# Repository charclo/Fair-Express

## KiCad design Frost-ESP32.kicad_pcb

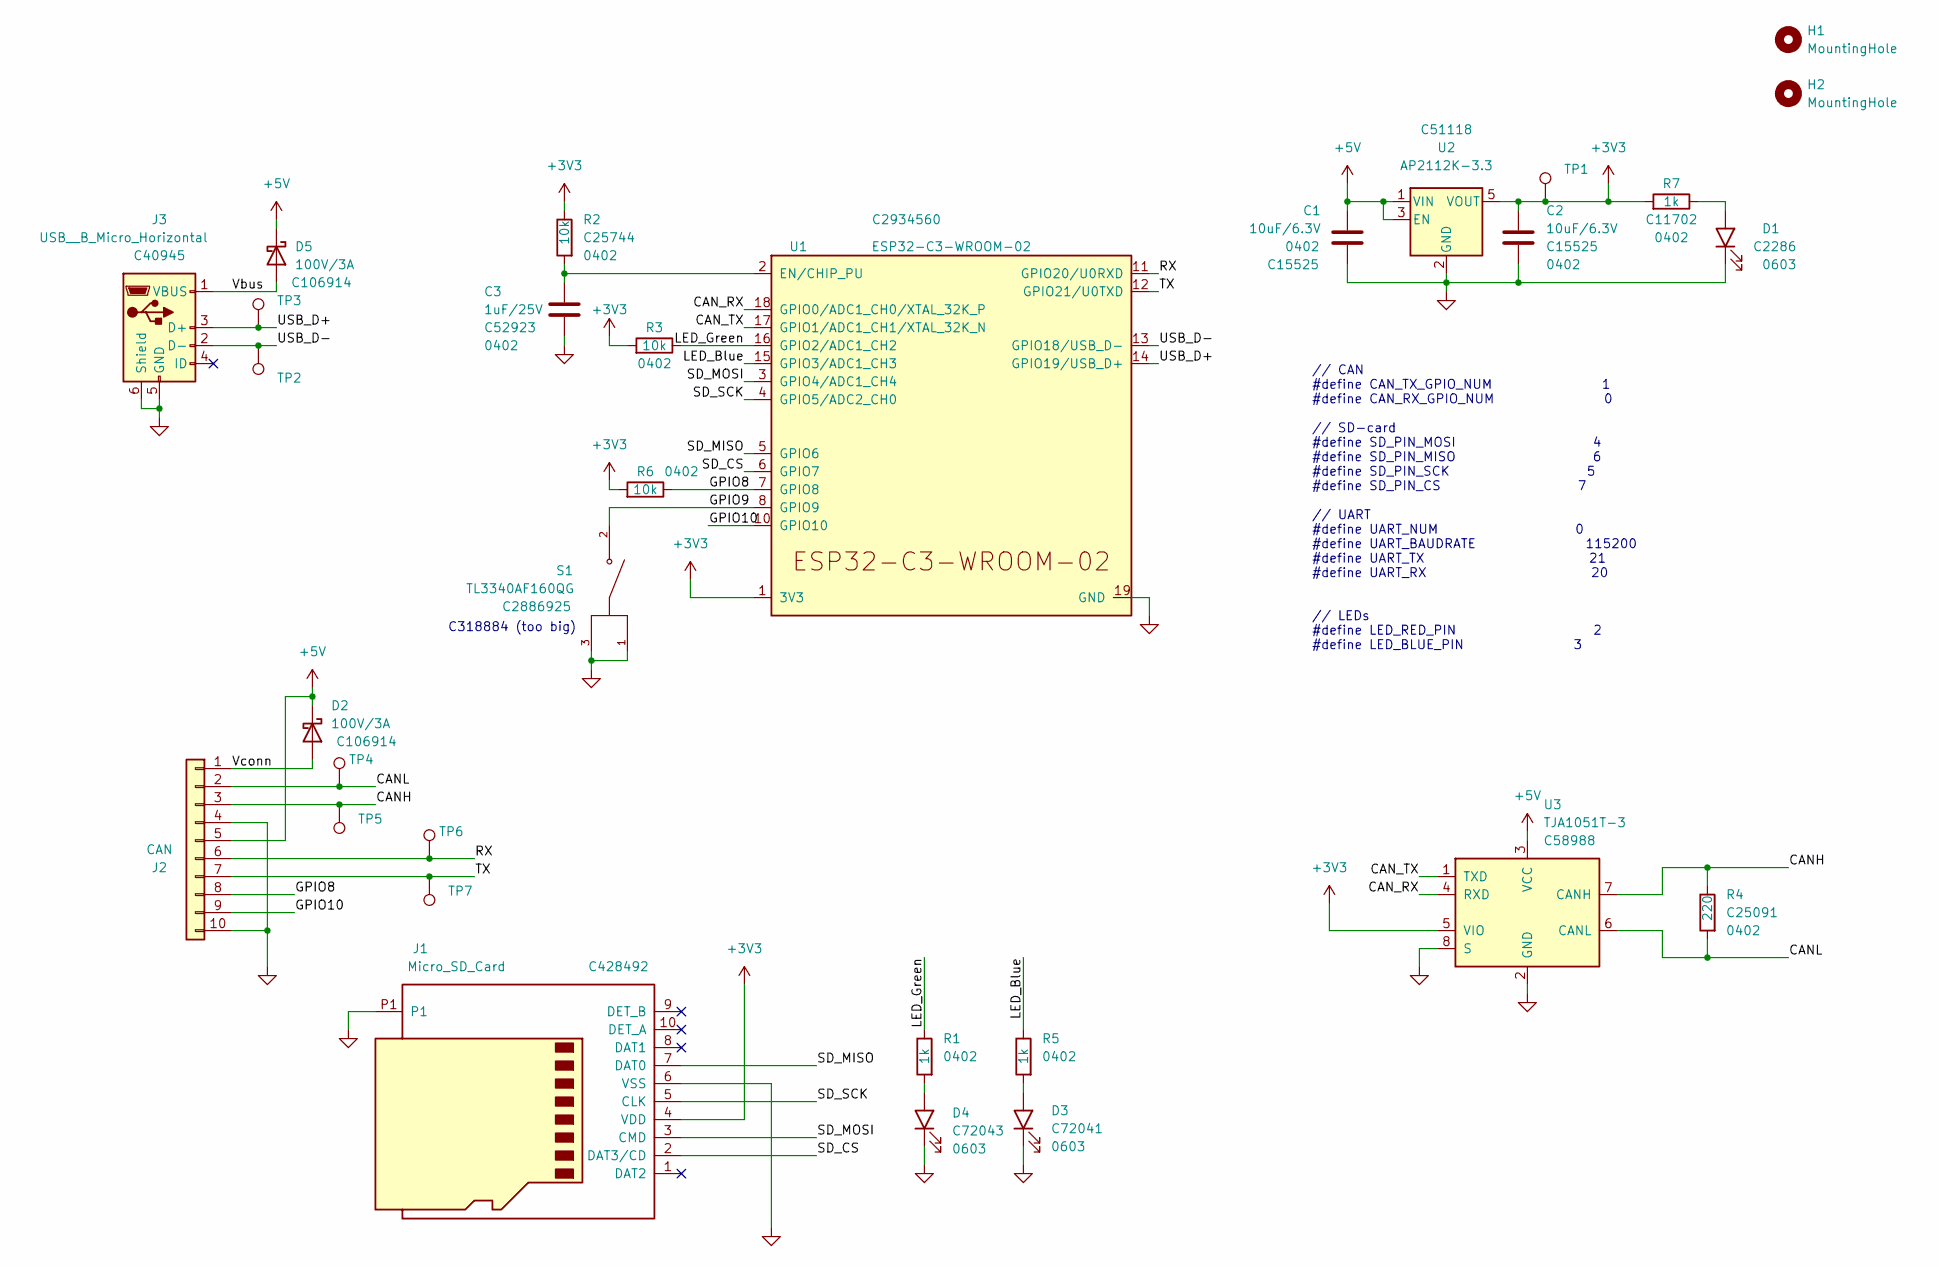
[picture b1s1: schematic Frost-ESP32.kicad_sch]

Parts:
C1, C2: 10uF/6.3V; C_0402_1005Metric; LCSC C15525
C3: 1uF/25V; C_0402_1005Metric; LCSC C52923
D1: Red; LED_0603_1608Metric; LCSC C2286
D2, D5: 100V/3A; D_SOD-123F; LCSC C106914
D3: Blue; LED_0603_1608Metric; LCSC C72041
D4: Emerald; LED_0603_1608Metric; LCSC C72043
H1, H2: MountingHole; MountingHole_3.2mm_M3
J1: Micro_SD_Card; MOLEX_503398-1892; LCSC C428492
J2: CAN; PinHeader_1x10_P1.27mm_Vertical
J3: USB__B_Micro_Horizontal; USB_Micro-B_Molex_47346-0001; LCSC C40945
R1, R5, R7: 1k; R_0402_1005Metric; LCSC C11702
R2, R3, R6: 10k; R_0402_1005Metric; LCSC C25744
R4: 220; R_0402_1005Metric; LCSC C25091
S1: TL3340AF160QG; SW_TL3340AF160QG; LCSC C2886925
TP1, TP2, TP3, TP4, TP5, TP6, TP7: TestPoint; TestPoint_Pad_D1.0mm
U1: ESP32-C3-WROOM-02; LCSC C2934560
U2: AP2112K-3.3; SOT-23-5; LCSC C51118
U3: TJA1051T-3; SOIC-8_3.9x4.9mm_P1.27mm; LCSC C58988

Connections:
+3V3: C2.1, J1.4 (VDD), R2.2, R3.1, R6.1, R7.1, TP1.1, U1.1 (3V3), U2.5 (VOUT), U3.5 (VIO)
+5V: C1.1, D2.1 (K), D5.1 (K), J2.5, U2.1 (VIN), U2.3 (EN), U3.3 (VCC)
/CANH: J2.3, R4.2, TP5.1, U3.7 (CANH)
/CANL: J2.2, R4.1, TP4.1, U3.6 (CANL)
/CAN_RX: U1.18 (GPIO0/ADC1_CH0/XTAL_32K_P), U3.4 (RXD)
/CAN_TX: U1.17 (GPIO1/ADC1_CH1/XTAL_32K_N), U3.1 (TXD)
/GPIO8: J2.8, R6.2, U1.7 (GPIO8)
/GPIO9: S1.2, U1.8 (GPIO9)
/GPIO10: J2.9, U1.10 (GPIO10)
/LED_Blue: R5.2, U1.15 (GPIO3/ADC1_CH3)
/LED_Green: R1.2, R3.2, U1.16 (GPIO2/ADC1_CH2)
/RX: J2.6, TP6.1, U1.11 (GPIO20/U0RXD)
/SD_CS: J1.2 (DAT3/CD), U1.6 (GPIO7)
/SD_MISO: J1.7 (DAT0), U1.5 (GPIO6)
/SD_MOSI: J1.3 (CMD), U1.3 (GPIO4/ADC1_CH4)
/SD_SCK: J1.5 (CLK), U1.4 (GPIO5/ADC2_CH0)
/TX: J2.7, TP7.1, U1.12 (GPIO21/U0TXD)
/USB_D+: J3.3 (D+), TP3.1, U1.14 (GPIO19/USB_D+)
/USB_D-: J3.2 (D-), TP2.1, U1.13 (GPIO18/USB_D-)
/Vbus: D5.2 (A), J3.1 (VBUS)
/Vconn: D2.2 (A), J2.1
GND: C1.2, C2.2, C3.2, D1.1 (K), D3.1 (K), D4.1 (K), J1.6 (VSS), J1.P1, J2.4, J2.10, J3.5 (GND), J3.6 (Shield), S1.1, S1.3, U1.9 (GND), U1.19 (GND), U2.2 (GND), U3.2 (GND), U3.8 (S)
unnamed: D1.2 (A), R7.2
unnamed: D3.2 (A), R5.1
unnamed: D4.2 (A), R1.1
unnamed: C3.1, R2.1, U1.2 (EN/CHIP_PU)

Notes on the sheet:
// CAN #define CAN_TX_GPIO_NUM 1 #define CAN_RX_GPIO_NUM 0 // SD-card #define SD_PIN_MOSI 4 #define SD_PIN_MISO 6 #define SD_PIN_SCK 5 #define SD_PIN_CS 7 // UART #define UART_NUM 0 #define UART_BAUDRATE 115200 #define UART_TX 21 #define UART_RX 20
C318884 (too big)
// LEDs #define LED_RED_PIN 2 #define LED_BLUE_PIN 3

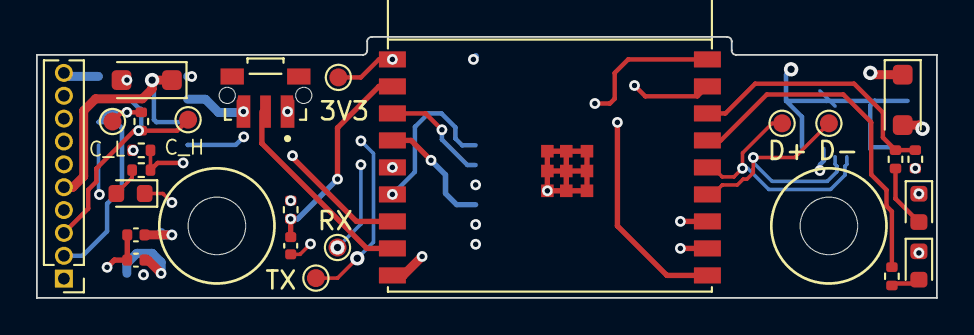
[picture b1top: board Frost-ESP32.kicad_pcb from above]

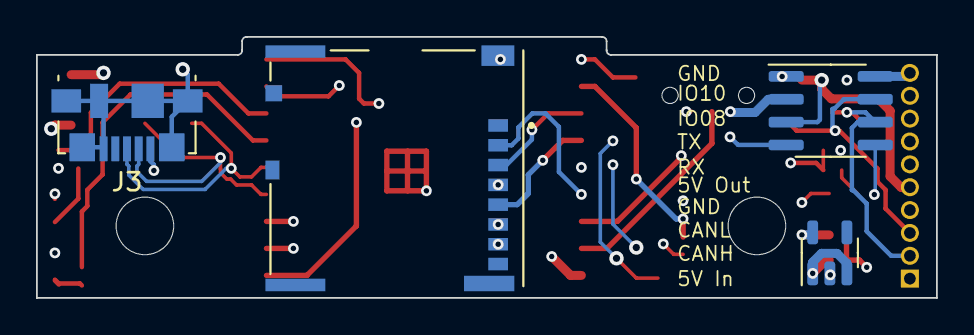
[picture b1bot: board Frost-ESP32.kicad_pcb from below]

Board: 6 copper layers, 50.0 x 14.5 mm, 31 parts (4 on the bottom side), 26 nets.

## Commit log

2023-11-03 moved some symbols to fair library
2024-01-29 After ordering v0.1
